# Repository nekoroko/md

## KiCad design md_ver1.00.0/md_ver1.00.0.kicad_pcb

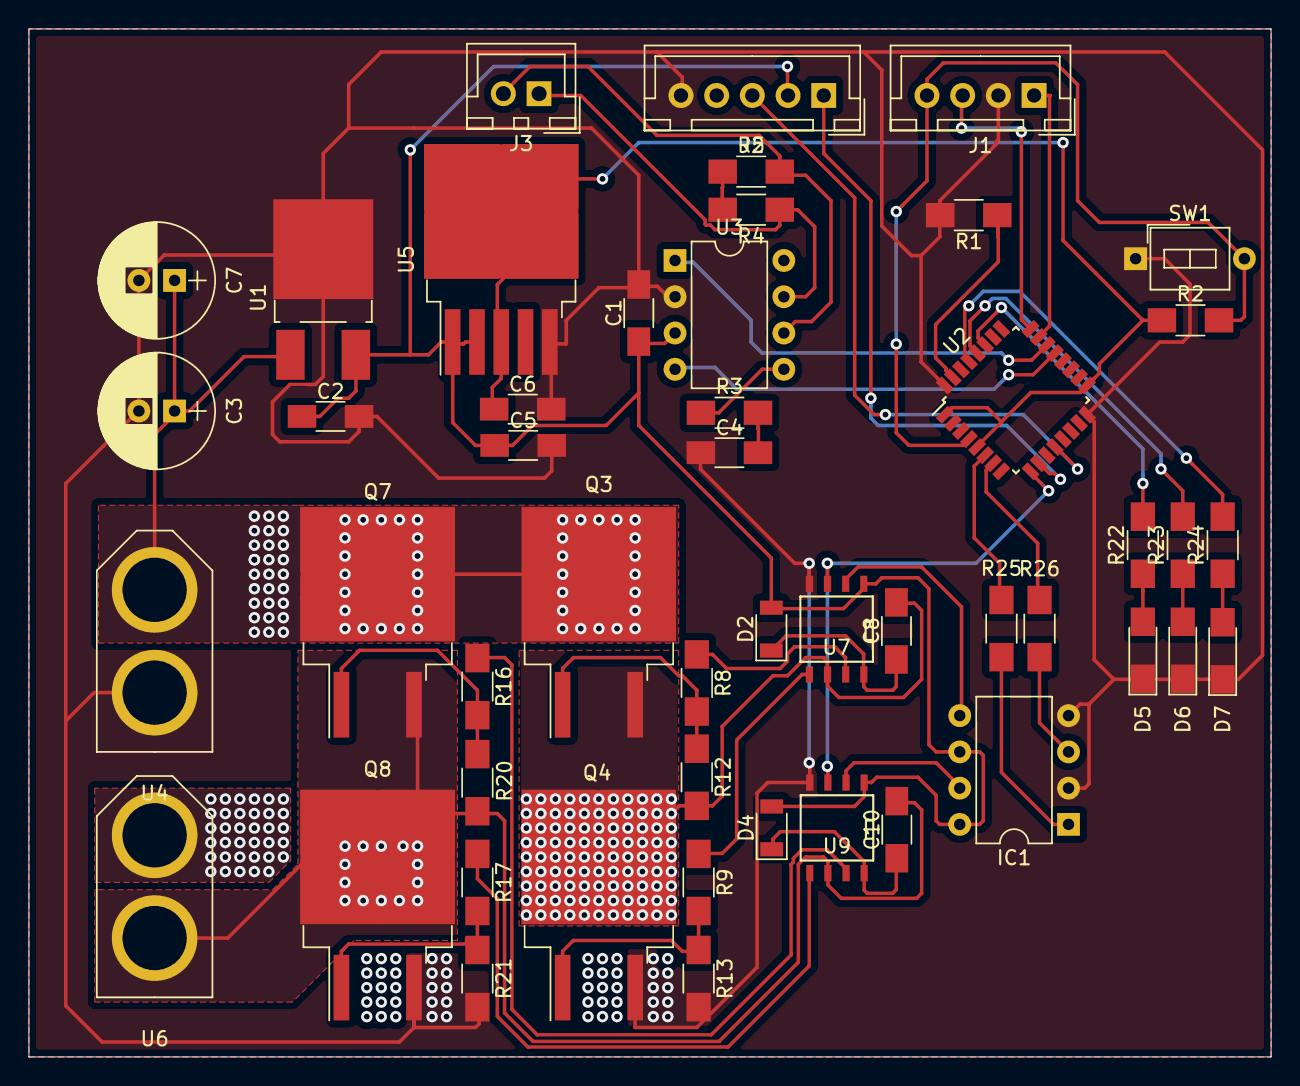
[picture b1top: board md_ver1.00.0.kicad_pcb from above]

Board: 2 copper layers, 87.0 x 72.0 mm, 49 parts (0 on the bottom side), 42 nets.

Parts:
C1: 0.1uF; C_1206_HandSoldering
C2: 0.1u; C_1206_HandSoldering
C3, C7: CP; CP_Radial_D8.0mm_P2.50mm
C4: 4700pF; C_1206_HandSoldering
C5: 0.33u; C_1206_HandSoldering
C6: 47u; C_1206_HandSoldering
C8, C10: 10u; C_1206_HandSoldering
D2, D4: 1N4148; D_1206
D5, D6, D7: LED; LED_1206_HandSoldering
IC1: TLP621-2; DIP-8_W7.62mm
J1: Conn_01x04; JST_XH_B04B-XH-A_04x2.50mm_Straight
J2: Conn_01x05; JST_XH_B05B-XH-A_05x2.50mm_Straight
J3: Conn_01x02; JST_XH_B02B-XH-A_02x2.50mm_Straight
Q3, Q4, Q7, Q8: SKI03036; TO-263-2
R1, R2, R12, R13, R20, R21, R22, R23, R24: 10k; R_1206_HandSoldering
R3: 300; R_1206_HandSoldering
R4, R5: 60; R_1206_HandSoldering
R8, R9, R16, R17: 10; R_1206_HandSoldering
R25, R26: 220; R_1206_HandSoldering
SW1: SW_Push; SW_DIP_x1_W7.62mm_Slide_LowProfile
U1: NJM7800S; TO-252-2_Rectifier
U2: STM32F303K8Tx; LQFP-32_7x7mm_Pitch0.8mm
U3: MCP2561-E-P; DIP-8_W7.62mm
U4, U6: XT-60
U5: PQ033EZ1HZ; TO-263-5_TabPin6
U7, U9: IR2104; SOIC-8-N

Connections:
+3V3: C6.1, R2.1, U2.1, U2.5, U2.17, U5.3, U5.6
+5V: C1.1, C2.1, C5.1, D2.2, D4.2, IC1.6, IC1.8, J2.2, U1.3, U3.3, U5.1, U5.2, U7.1, U9.1
A_1: J2.3, U2.12
B_1: J2.1, U2.10
CANH: J3.1, R4.1, U3.7
CANL: J3.2, R5.2, U3.6
GND: C1.2, C2.2, C3.2, C4.1, C5.2, C6.2, C7.2, D5.1, D6.1, D7.1, IC1.2, IC1.4, J1.2, J2.5, Q4.3, Q8.3, R1.2, R13.2, R21.2, SW1.1, U1.2, U2.16, U2.32, U3.2, U4.2, U5.5, U7.4, U9.4
M_HIGHSIDE1: C8.2, Q3.3, Q4.2, R12.2, U6.1, U7.6
M_LOWSIDE1: C10.2, Q7.3, Q8.2, R20.2, U6.2, U9.6
NRST: J1.4, R2.2, SW1.2, U2.4
unnamed: C4.2, R3.2
unnamed: C8.1, D2.1, U7.8
unnamed: C10.1, D4.1, U9.8
unnamed: D5.2, R22.1
unnamed: D6.2, R23.1
unnamed: D7.2, R24.1
unnamed: IC1.1, R25.2
unnamed: IC1.3, R26.2
unnamed: Q3.1, R8.2, R12.1
unnamed: Q4.1, R9.2, R13.1
unnamed: Q7.1, R16.2, R20.1
unnamed: Q8.1, R17.2, R21.1
unnamed: R1.1, U2.31
unnamed: R3.1, U3.5
unnamed: R4.2, R5.1
unnamed: R8.1, U7.7
unnamed: R9.1, U7.5
unnamed: R16.1, U9.7
unnamed: R17.1, U9.5
unnamed: R22.2, U2.27
unnamed: R23.2, U2.28
unnamed: R24.2, U2.29
RXD: U2.21, U3.4
SD: U2.9, U7.3, U9.3
SWCLK: J1.1, U2.23
SWDIO: J1.3, U2.24
TXD: U2.22, U3.1
VDD: C3.1, C7.1, Q3.2, Q7.2, U1.1, U4.1
pwm1: R26.1, U2.7
pwm2: R25.1, U2.6
pwm_5v_out_1: IC1.5, U7.2
pwm_5v_out_2: IC1.7, U9.2

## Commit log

2019-09-02 [new]first commit
